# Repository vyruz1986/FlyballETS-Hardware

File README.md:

## FlyballETS-Hardware

The FlyballETS-Hardware project is a subproject of the [Flyball ETS project](https://www.sparkydevices.com/tag/flyball-ets/).
It contains the designs for the electronic hardware which is required to build the Flyball-ETS project.

## Design Files

The design files are in KiCAD format, and consist of several files:
* FlyballETS-Board.sch/kicad_pcb: Schematic and board file for the PCB of Flyball ETS
* FlyballETS-Board-BOM.txt: Bill of materials used to know which components to order and where to solder them on the board

These files can be used by people who want to improve or change the design.

## Export Files
`Exports/FlyballETS-Board-BRD/SCH.png` are picture exports of the design files so people can view them without needing to install EAGLE

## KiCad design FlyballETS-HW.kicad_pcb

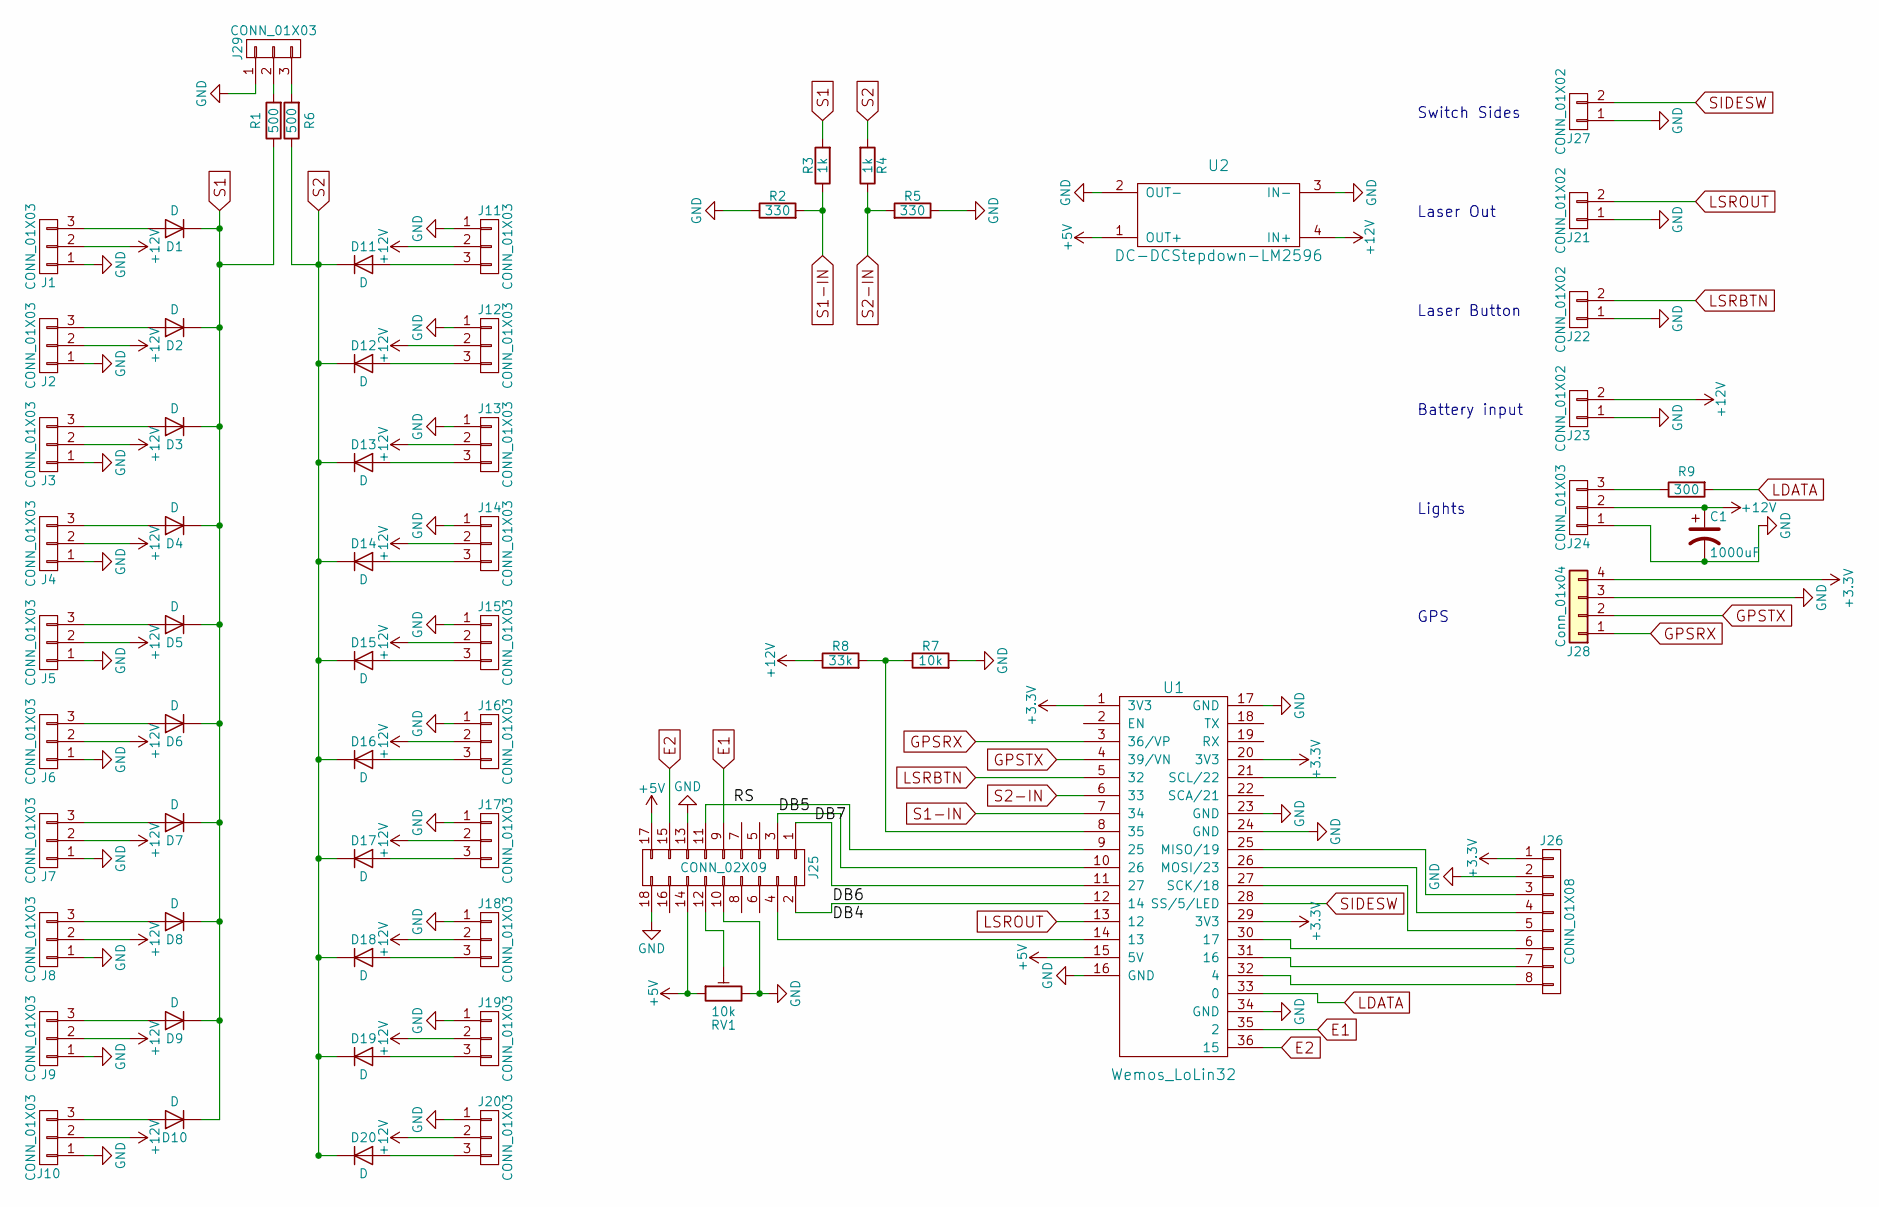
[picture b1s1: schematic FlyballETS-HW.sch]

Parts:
C1: 1000uF; CP_Radial_D10.0mm_P5.00mm
D1, D2, D3, D4, D5, D6, D7, D8, D9, D10, D11, D12, D13, D14, D15, D16, D17, D18, D19, D20: D; D_DO-35_SOD27_P7.62mm_Horizontal
J1, J2, J3, J4, J5, J6, J7, J8, J9, J10, J11, J12, J13, J14, J15, J16, J17, J18, J19, J20, J24, J29: CONN_01X03; JST_XH_B03B-XH-A_03x2.50mm_Straight
J21, J22, J23, J27: CONN_01X02; JST_XH_B02B-XH-A_02x2.50mm_Straight
J25: CONN_02X09; IDC_Header_Straight_18pins
J26: CONN_01X08; Pin_Header_Straight_1x08_Pitch2.54mm
J28: Conn_01x04; Pin_Header_Angled_1x04_Pitch2.54mm
R1, R6: 500; R_Axial_DIN0207_L6.3mm_D2.5mm_P7.62mm_Horizontal
R2, R5: 330; R_Axial_DIN0207_L6.3mm_D2.5mm_P7.62mm_Horizontal
R3, R4: 1k; R_Axial_DIN0207_L6.3mm_D2.5mm_P7.62mm_Horizontal
R7: 10k; R_Axial_DIN0207_L6.3mm_D2.5mm_P7.62mm_Horizontal
R8: 33k; R_Axial_DIN0207_L6.3mm_D2.5mm_P7.62mm_Horizontal
R9: 300; R_Axial_DIN0207_L6.3mm_D2.5mm_P7.62mm_Horizontal
RV1: 10k; R_TRIM_3362P
U1: Wemos_LoLin32; LoLin_32_Board
U2: DC-DCStepdown-LM2596; LM2596-DC-DC-Stepdown-Module

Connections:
+3V3: J26.1, J28.4, U1.1 (3V3), U1.20 (3V3), U1.29 (3V3)
+5V: J25.14, J25.17, RV1.1, U1.15 (5V), U2.1 (OUT+)
+12V: C1.1, J1.2, J2.2, J3.2, J4.2, J5.2, J6.2, J7.2, J8.2, J9.2, J10.2, J11.2, J12.2, J13.2, J14.2, J15.2, J16.2, J17.2, J18.2, J19.2, J20.2, J23.2, J24.2, R8.1, U2.4 (IN+)
/DB5: J25.3, U1.10 (26)
/DB6: J25.2, U1.12 (14)
/DB7: J25.1, U1.11 (27)
/RS: J25.11, U1.9 (25)
E1: J25.9, U1.35 (2)
E2: J25.15, U1.36 (15)
GND: C1.2, J1.1, J2.1, J3.1, J4.1, J5.1, J6.1, J7.1, J8.1, J9.1, J10.1, J11.1, J12.1, J13.1, J14.1, J15.1, J16.1, J17.1, J18.1, J19.1, J20.1, J21.1, J22.1, J23.1, J24.1, J25.10, J25.13, J25.18, J26.2, J27.1, J28.3, J29.1, R2.1, R5.1, R7.2, RV1.3, U1.16 (GND), U1.17 (GND), U1.23 (GND), U1.24 (GND), U1.34 (GND), U2.2 (OUT-), U2.3 (IN-)
GPSRX: J28.1, U1.3 (36/VP)
GPSTX: J28.2, U1.4 (39/VN)
LDATA: R9.2, U1.33 (0)
LSRBTN: J22.2, U1.5 (32)
LSROUT: J21.2, U1.13 (12)
unnamed: D1.2 (A), J1.3
unnamed: D2.2 (A), J2.3
unnamed: D3.2 (A), J3.3
unnamed: D4.2 (A), J4.3
unnamed: D5.2 (A), J5.3
unnamed: D6.2 (A), J6.3
unnamed: D7.2 (A), J7.3
unnamed: D8.2 (A), J8.3
unnamed: D9.2 (A), J9.3
unnamed: D10.2 (A), J10.3
unnamed: D11.2 (A), J11.3
unnamed: D12.2 (A), J12.3
unnamed: D13.2 (A), J13.3
unnamed: D14.2 (A), J14.3
unnamed: D15.2 (A), J15.3
unnamed: D16.2 (A), J16.3
unnamed: D17.2 (A), J17.3
unnamed: D18.2 (A), J18.3
unnamed: D19.2 (A), J19.3
unnamed: D20.2 (A), J20.3
unnamed: J24.3, R9.1
unnamed: J25.4, U1.14 (13)
unnamed: J25.12, RV1.2
unnamed: J26.3, U1.25 (MISO/19)
unnamed: J26.4, U1.26 (MOSI/23)
unnamed: J26.5, U1.27 (SCK/18)
unnamed: J26.6, U1.30 (17)
unnamed: J26.7, U1.31 (16)
unnamed: J26.8, U1.32 (4)
unnamed: J29.2, R1.2
unnamed: J29.3, R6.2
unnamed: R7.1, R8.2, U1.8 (35)
S1: D1.1 (K), D2.1 (K), D3.1 (K), D4.1 (K), D5.1 (K), D6.1 (K), D7.1 (K), D8.1 (K), D9.1 (K), D10.1 (K), R1.1, R3.2
S1-IN: R2.2, R3.1, U1.7 (34)
S2: D11.1 (K), D12.1 (K), D13.1 (K), D14.1 (K), D15.1 (K), D16.1 (K), D17.1 (K), D18.1 (K), D19.1 (K), D20.1 (K), R4.2, R6.1
S2-IN: R4.1, R5.2, U1.6 (33)
SIDESW: J27.2, U1.28 (SS/5/LED)

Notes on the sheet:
Laser Out
Laser Button
Battery input
Lights
Switch Sides
GPS

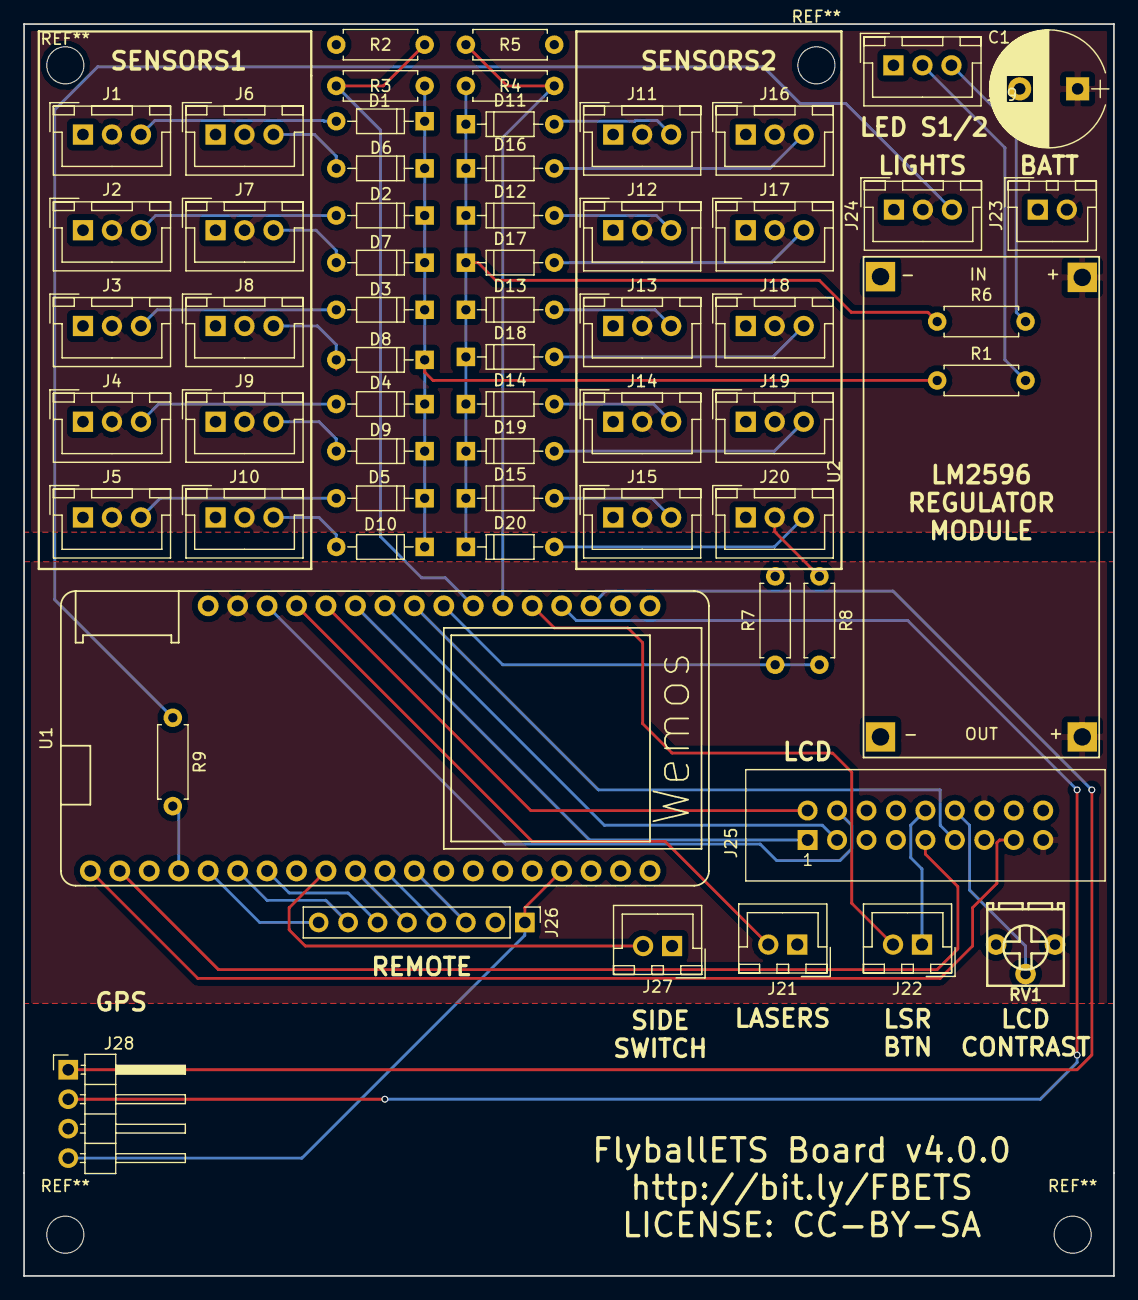
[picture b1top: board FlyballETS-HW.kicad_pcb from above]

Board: 2 copper layers, 94.0 x 108.0 mm, 62 parts (0 on the bottom side), 52 nets.

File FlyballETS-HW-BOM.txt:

Source:	C:/Users/alexg/OneDrive/Projects/Schematics/FlyballETS-Hardware/FlyballETS-HW.sch
Date:	06/28/18 22:32:41
Tool:	Eeschema 4.0.7
Component Count:	62
Ref	Value	Part	Footprint	Description	Vendor
C1	1000uF	device:CP1	Capacitors_THT:CP_Radial_D10.0mm_P5.00mm	Polarised capacitor	
D1	D	device:D	Diodes_THT:D_DO-35_SOD27_P7.62mm_Horizontal	Diode	
D2	D	device:D	Diodes_THT:D_DO-35_SOD27_P7.62mm_Horizontal	Diode	
D3	D	device:D	Diodes_THT:D_DO-35_SOD27_P7.62mm_Horizontal	Diode	
D4	D	device:D	Diodes_THT:D_DO-35_SOD27_P7.62mm_Horizontal	Diode	
D5	D	device:D	Diodes_THT:D_DO-35_SOD27_P7.62mm_Horizontal	Diode	
D6	D	device:D	Diodes_THT:D_DO-35_SOD27_P7.62mm_Horizontal	Diode	
D7	D	device:D	Diodes_THT:D_DO-35_SOD27_P7.62mm_Horizontal	Diode	
D8	D	device:D	Diodes_THT:D_DO-35_SOD27_P7.62mm_Horizontal	Diode	
D9	D	device:D	Diodes_THT:D_DO-35_SOD27_P7.62mm_Horizontal	Diode	
D10	D	device:D	Diodes_THT:D_DO-35_SOD27_P7.62mm_Horizontal	Diode	
D11	D	device:D	Diodes_THT:D_DO-35_SOD27_P7.62mm_Horizontal	Diode	
D12	D	device:D	Diodes_THT:D_DO-35_SOD27_P7.62mm_Horizontal	Diode	
D13	D	device:D	Diodes_THT:D_DO-35_SOD27_P7.62mm_Horizontal	Diode	
D14	D	device:D	Diodes_THT:D_DO-35_SOD27_P7.62mm_Horizontal	Diode	
D15	D	device:D	Diodes_THT:D_DO-35_SOD27_P7.62mm_Horizontal	Diode	
D16	D	device:D	Diodes_THT:D_DO-35_SOD27_P7.62mm_Horizontal	Diode	
D17	D	device:D	Diodes_THT:D_DO-35_SOD27_P7.62mm_Horizontal	Diode	
D18	D	device:D	Diodes_THT:D_DO-35_SOD27_P7.62mm_Horizontal	Diode	
D19	D	device:D	Diodes_THT:D_DO-35_SOD27_P7.62mm_Horizontal	Diode	
D20	D	device:D	Diodes_THT:D_DO-35_SOD27_P7.62mm_Horizontal	Diode	
J1	CONN_01X03	FlyballETS-HW-cache:CONN_01X03	Connectors_JST:JST_XH_B03B-XH-A_03x2.50mm_Straight		
J2	CONN_01X03	FlyballETS-HW-cache:CONN_01X03	Connectors_JST:JST_XH_B03B-XH-A_03x2.50mm_Straight		
J3	CONN_01X03	FlyballETS-HW-cache:CONN_01X03	Connectors_JST:JST_XH_B03B-XH-A_03x2.50mm_Straight		
J4	CONN_01X03	FlyballETS-HW-cache:CONN_01X03	Connectors_JST:JST_XH_B03B-XH-A_03x2.50mm_Straight		
J5	CONN_01X03	FlyballETS-HW-cache:CONN_01X03	Connectors_JST:JST_XH_B03B-XH-A_03x2.50mm_Straight		
J6	CONN_01X03	FlyballETS-HW-cache:CONN_01X03	Connectors_JST:JST_XH_B03B-XH-A_03x2.50mm_Straight		
J7	CONN_01X03	FlyballETS-HW-cache:CONN_01X03	Connectors_JST:JST_XH_B03B-XH-A_03x2.50mm_Straight		
J8	CONN_01X03	FlyballETS-HW-cache:CONN_01X03	Connectors_JST:JST_XH_B03B-XH-A_03x2.50mm_Straight		
J9	CONN_01X03	FlyballETS-HW-cache:CONN_01X03	Connectors_JST:JST_XH_B03B-XH-A_03x2.50mm_Straight		
J10	CONN_01X03	FlyballETS-HW-cache:CONN_01X03	Connectors_JST:JST_XH_B03B-XH-A_03x2.50mm_Straight		
J11	CONN_01X03	FlyballETS-HW-cache:CONN_01X03	Connectors_JST:JST_XH_B03B-XH-A_03x2.50mm_Straight		
J12	CONN_01X03	FlyballETS-HW-cache:CONN_01X03	Connectors_JST:JST_XH_B03B-XH-A_03x2.50mm_Straight		
J13	CONN_01X03	FlyballETS-HW-cache:CONN_01X03	Connectors_JST:JST_XH_B03B-XH-A_03x2.50mm_Straight		
J14	CONN_01X03	FlyballETS-HW-cache:CONN_01X03	Connectors_JST:JST_XH_B03B-XH-A_03x2.50mm_Straight		
J15	CONN_01X03	FlyballETS-HW-cache:CONN_01X03	Connectors_JST:JST_XH_B03B-XH-A_03x2.50mm_Straight		
J16	CONN_01X03	FlyballETS-HW-cache:CONN_01X03	Connectors_JST:JST_XH_B03B-XH-A_03x2.50mm_Straight		
J17	CONN_01X03	FlyballETS-HW-cache:CONN_01X03	Connectors_JST:JST_XH_B03B-XH-A_03x2.50mm_Straight		
J18	CONN_01X03	FlyballETS-HW-cache:CONN_01X03	Connectors_JST:JST_XH_B03B-XH-A_03x2.50mm_Straight		
J19	CONN_01X03	FlyballETS-HW-cache:CONN_01X03	Connectors_JST:JST_XH_B03B-XH-A_03x2.50mm_Straight		
J20	CONN_01X03	FlyballETS-HW-cache:CONN_01X03	Connectors_JST:JST_XH_B03B-XH-A_03x2.50mm_Straight		
J21	CONN_01X02	FlyballETS-HW-cache:CONN_01X02	Connectors_JST:JST_XH_B02B-XH-A_02x2.50mm_Straight		
J22	CONN_01X02	FlyballETS-HW-cache:CONN_01X02	Connectors_JST:JST_XH_B02B-XH-A_02x2.50mm_Straight		
J23	CONN_01X02	FlyballETS-HW-cache:CONN_01X02	Connectors_JST:JST_XH_B02B-XH-A_02x2.50mm_Straight		
J24	CONN_01X03	FlyballETS-HW-cache:CONN_01X03	Connectors_JST:JST_XH_B03B-XH-A_03x2.50mm_Straight		
J25	CONN_02X09	FlyballETS-HW-cache:CONN_02X09	MyStuff:IDC_Header_Straight_18pins		
J26	CONN_01X08	FlyballETS-HW-cache:CONN_01X08	Pin_Headers:Pin_Header_Straight_1x08_Pitch2.54mm		
J27	CONN_01X02	FlyballETS-HW-cache:CONN_01X02	Connectors_JST:JST_XH_B02B-XH-A_02x2.50mm_Straight		
J28	Conn_01x04	conn:Conn_01x04	Pin_Headers:Pin_Header_Angled_1x04_Pitch2.54mm	Generic connector, single row, 01x04	
J29	CONN_01X03	FlyballETS-HW-cache:CONN_01X03	Connectors_JST:JST_XH_B03B-XH-A_03x2.50mm_Straight		
R1	500	device:R	Resistors_THT:R_Axial_DIN0207_L6.3mm_D2.5mm_P7.62mm_Horizontal	Resistor	
R2	330	device:R	Resistors_THT:R_Axial_DIN0207_L6.3mm_D2.5mm_P7.62mm_Horizontal	Resistor	
R3	1k	device:R	Resistors_THT:R_Axial_DIN0207_L6.3mm_D2.5mm_P7.62mm_Horizontal	Resistor	
R4	1k	device:R	Resistors_THT:R_Axial_DIN0207_L6.3mm_D2.5mm_P7.62mm_Horizontal	Resistor	
R5	330	device:R	Resistors_THT:R_Axial_DIN0207_L6.3mm_D2.5mm_P7.62mm_Horizontal	Resistor	
R6	500	device:R	Resistors_THT:R_Axial_DIN0207_L6.3mm_D2.5mm_P7.62mm_Horizontal	Resistor	
R7	10k	device:R	Resistors_THT:R_Axial_DIN0207_L6.3mm_D2.5mm_P7.62mm_Horizontal	Resistor	
R8	33k	device:R	Resistors_THT:R_Axial_DIN0207_L6.3mm_D2.5mm_P7.62mm_Horizontal	Resistor	
R9	300	device:R	Resistors_THT:R_Axial_DIN0207_L6.3mm_D2.5mm_P7.62mm_Horizontal	Resistor	
RV1	10k	device:POT_TRIM	MyModules:R_TRIM_3362P	Trim-Potentiometer	
U1	Wemos_LoLin32	FlyballETS-HW-cache:Wemos_LoLin32	Wemos:LoLin_32_Board		
U2	DC-DCStepdown-LM2596	MyStuff:DC-DCStepdown-LM2596	MyStuff:LM2596-DC-DC-Stepdown-Module

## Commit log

2015-08-30 Cleaned up mainboard design
2015-08-31 Added power board files
2015-09-01 Removed leftover AutoRouter statistics file
2015-09-01 Updated readme to include PWR board description
2015-09-01 Updated drawings and added PNG exports
    - Added frames around drawings to make it look neater
    - Added PNG export files so people who don't have EAGLE can see
    everything
2015-09-05 Corrected unrouted airwire
    The SensorsBoard had an unrouted airwire, this has been corrected
2015-12-20 Mainboard v2
    - Changed connectors to use JST-XH type
    - For LCD screen use flatcable/ribboncable connector (2x9 pins)
    - Repositioned everything to allow for smaller board size (12% smaller)
2015-12-20 Ignore eagle autorouter files
2015-12-30 Minor updates + added BOMs
    - Updated to EAGLE 7.5.0
    - Added BOM text file exports
    - Renamed arduino socket on MBD board
2015-12-30 Incorrect capacitor value
    Changed 100nF to 100uF
2016-01-10 v2 release of remaining boards.
    - Lightsboard: Corrected swapped pin connections on L2 side and made
    smaller
    - Powerboard: Made smaller and added descriptions for LM2596 board
    - Sensorboard: Made smaller
    - All boards: Removed JST connector type names
2016-03-02 LightsBoard:Fix 74HC595 problems
    Closes #5
    - Added decoupling capacitor over GND and VCC of 74HC595
    - Added missing connection of 74HC595 pin10 to +5V
2016-03-13 Changed resistor values to more practical ones
    Changed R1 to 5.6kOhm, R2 to 3.9kOhm. These are common values in
    resistor assortments. Fixes #2
2016-05-10 Fixed several issues
    - Checked all mounting holes (fixes #1 )
    - Marked light colors on lights PCB (fixes #7 )
    - Swapped pins 2 and 3 on LIGHTS connected on PWR board (fixes #3 )
2017-08-12 Fixed JST XH pin numbering
    Updated bt_con-jst-xh.lbr library with swapped pin numbering.
    Updated all board designs with updated library so they have the
    connectors the right way around
    Fixes #4
2017-08-23 Added one board to rule them all :)
2017-09-18 First revision ESP32 board
    Switched to KiCAD for schematic & PCB design
    Remade board as it was with ARduino Pro Mini but put ESP32 socket in place.
    Also added connector for GPS module which I want to use for time synchronisation
2017-10-25 Final changes for v4 release
    - Corrected README
    - Removed obsolete schematics, boards and export pictures
    - Added export for schematic
2017-10-25 Updated README for kicad
    We switched from EAGLE to KiCAD so the readme should reflect this
2017-10-25 Updated gitignore for KiCAD
2017-10-25 Delete FlyballETS-HW.kicad_pcb-bak
    This file should not have been committed
2017-10-25 Delete FlyballETS-HW.bak
    This file should not have been committed
2017-10-25 Added KiCAD project file
2017-10-25 Fixed some prototype problems
    - Ran final DRC to fix copper planes (fixes #9)
    - R1 pad 1 was connected to GND (fixes #10)
    - Changed Q1 and Q2 to TO-92 inline wide footprint (fixes #11)
2017-10-25 Fixed 3D settings of remote connector
    It was rotated and offset incorrectly
2018-04-23 Corrected GPS connections
2018-06-20 Fixed smaller issues
    - Added mounting holes
    - Added 1000uF cap for Ws2811 lights
    - Added 300R resistor in WS2811 data line
    - Removed transistors to invert sensor signal (we need to use NPN, NO from now on)
2018-08-04 Final version

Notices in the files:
FlyballETS-HW.kicad_pcb:
LICENSE: CC-BY-SA
